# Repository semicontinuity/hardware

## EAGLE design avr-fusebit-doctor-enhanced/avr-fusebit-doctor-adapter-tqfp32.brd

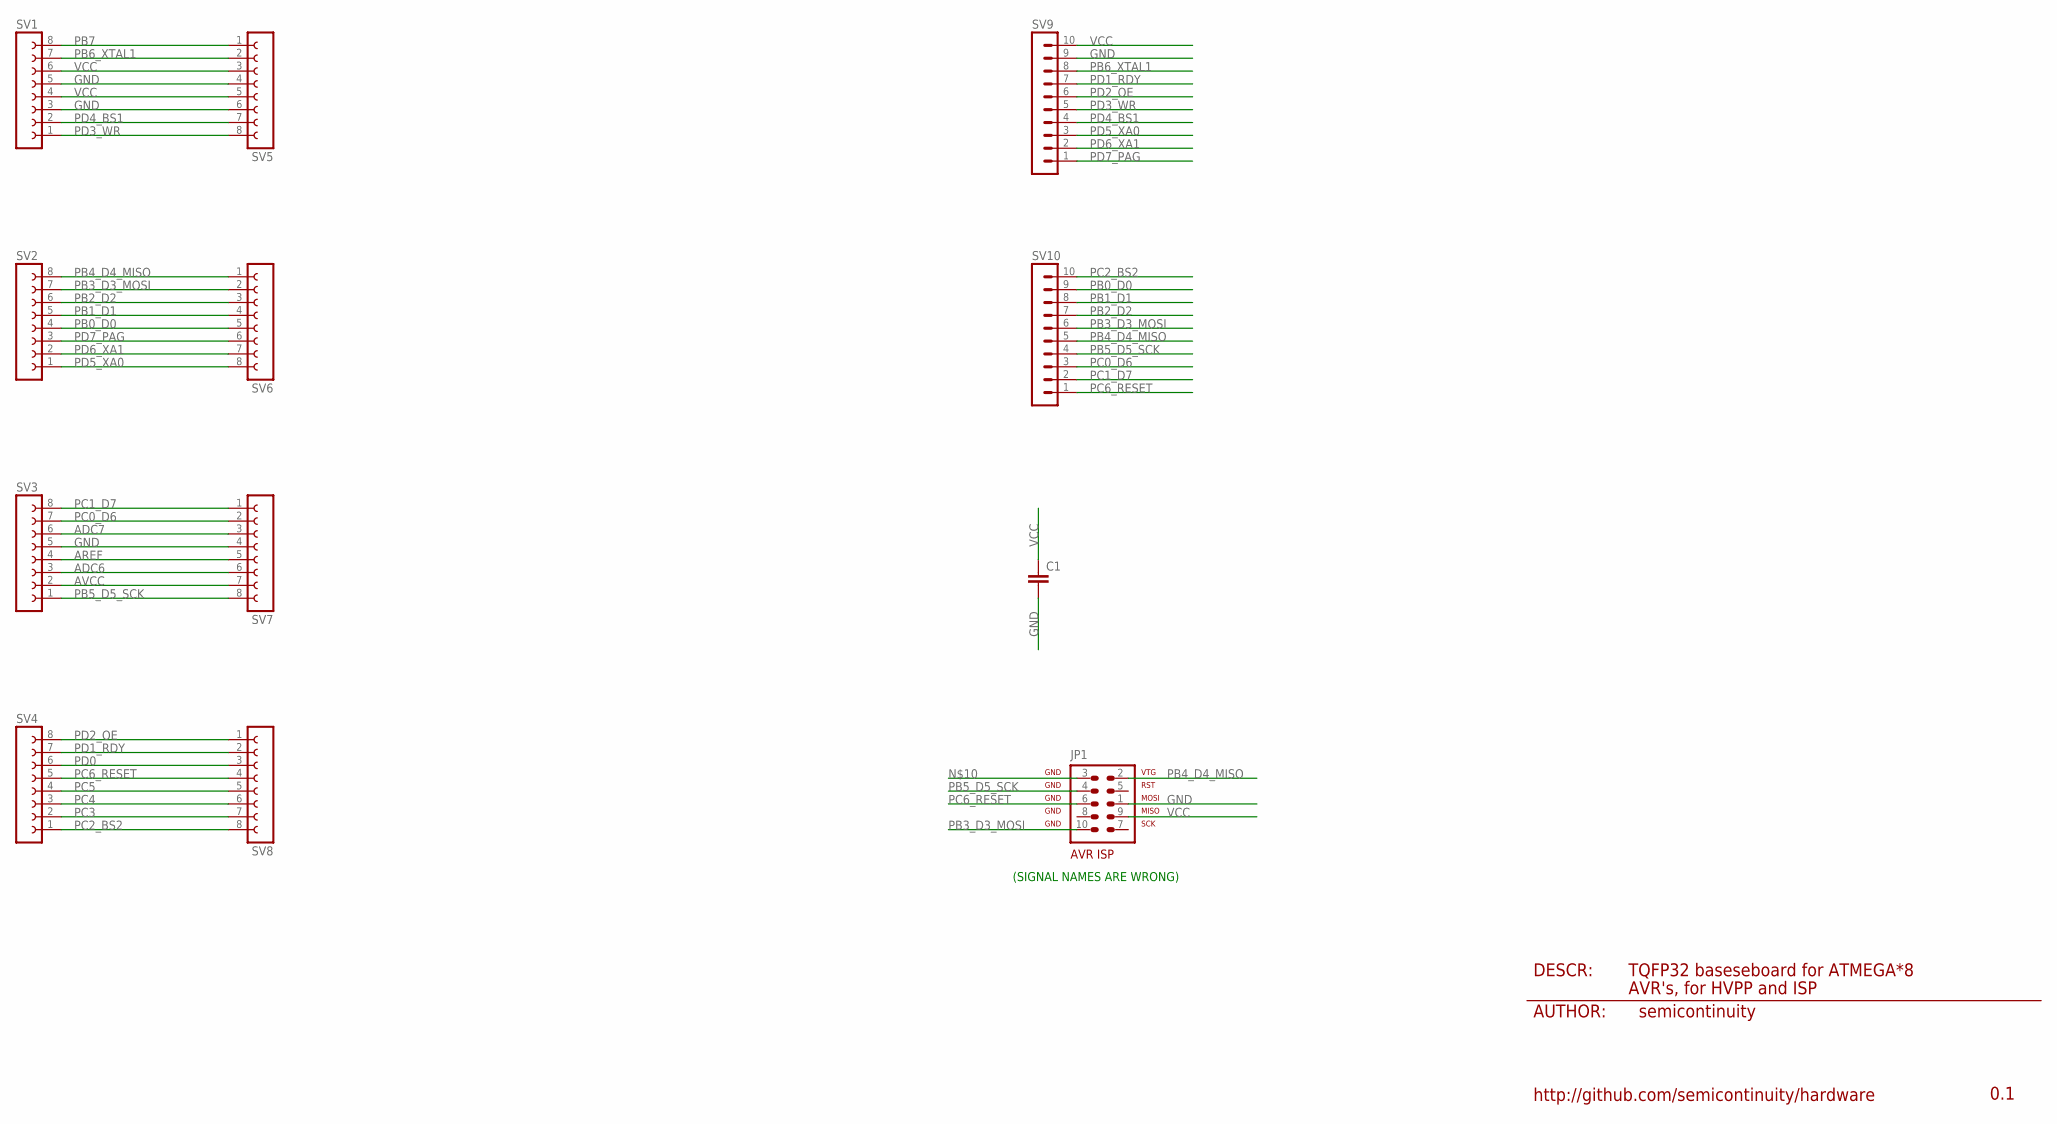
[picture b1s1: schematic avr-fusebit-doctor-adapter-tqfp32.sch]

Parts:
C1: C-EUC0805; C0805
JP1: AVR-ISP-10
SV1, SV2, SV3, SV4, SV5, SV6, SV7, SV8: FE08-1; FE08
SV9, SV10: MA10-1

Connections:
ADC6: SV3.3, SV7.6
ADC7: SV3.6, SV7.3
AREF: SV3.4, SV7.5
AVCC: SV3.2, SV7.7
GND: C1.2, JP1.1, SV1.3, SV1.5, SV3.5, SV5.4, SV5.6, SV7.4, SV9.9
PB0_D0: SV2.4, SV6.5, SV10.9
PB1_D1: SV2.5, SV6.4, SV10.8
PB2_D2: SV2.6, SV6.3, SV10.7
PB3_D3_MOSI: JP1.10, SV2.7, SV6.2, SV10.6
PB4_D4_MISO: JP1.2, SV2.8, SV6.1, SV10.5
PB5_D5_SCK: JP1.4, SV3.1, SV7.8, SV10.4
PB6_XTAL1: SV1.7, SV5.2, SV9.8
PB7: SV1.8, SV5.1
PC0_D6: SV3.7, SV7.2, SV10.3
PC1_D7: SV3.8, SV7.1, SV10.2
PC2_BS2: SV4.1, SV8.8, SV10.10
PC3: SV4.2, SV8.7
PC4: SV4.3, SV8.6
PC5: SV4.4, SV8.5
PC6_RESET: JP1.6, SV4.5, SV8.4, SV10.1
PD0: SV4.6, SV8.3
PD1_RDY: SV4.7, SV8.2, SV9.7
PD2_OE: SV4.8, SV8.1, SV9.6
PD3_WR: SV1.1, SV5.8, SV9.5
PD4_BS1: SV1.2, SV5.7, SV9.4
PD5_XA0: SV2.1, SV6.8, SV9.3
PD6_XA1: SV2.2, SV6.7, SV9.2
PD7_PAG: SV2.3, SV6.6, SV9.1
VCC: C1.1, JP1.9, SV1.4, SV1.6, SV5.3, SV5.5, SV9.10

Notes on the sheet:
AUTHOR:
DESCR:
TQFP32 baseseboard for ATMEGA*8
AVR's, for HVPP and ISP
semicontinuity
0.1
http://github.com/semicontinuity/hardware
(SIGNAL NAMES ARE WRONG)

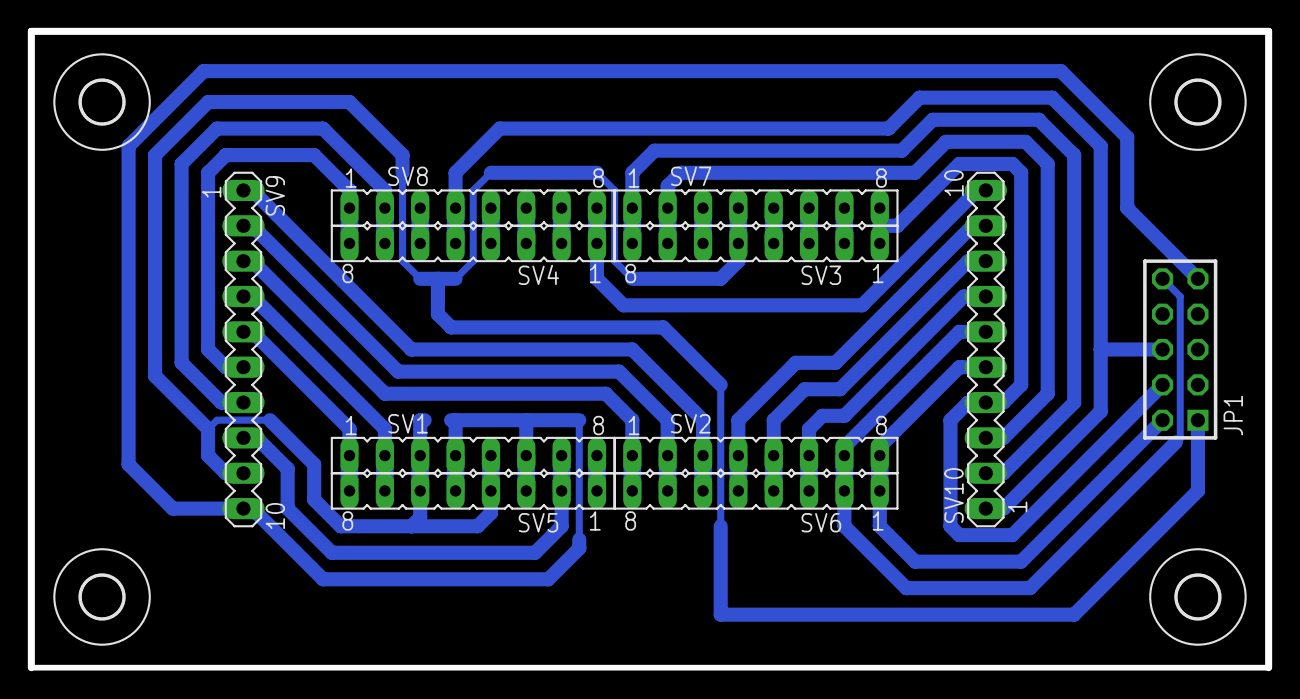
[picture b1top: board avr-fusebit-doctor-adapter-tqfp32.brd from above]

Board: 2 copper layers, 88.9 x 45.7 mm, 16 parts (1 on the bottom side), 29 nets.

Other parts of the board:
U$1, U$2, U$3, U$4: 3,0

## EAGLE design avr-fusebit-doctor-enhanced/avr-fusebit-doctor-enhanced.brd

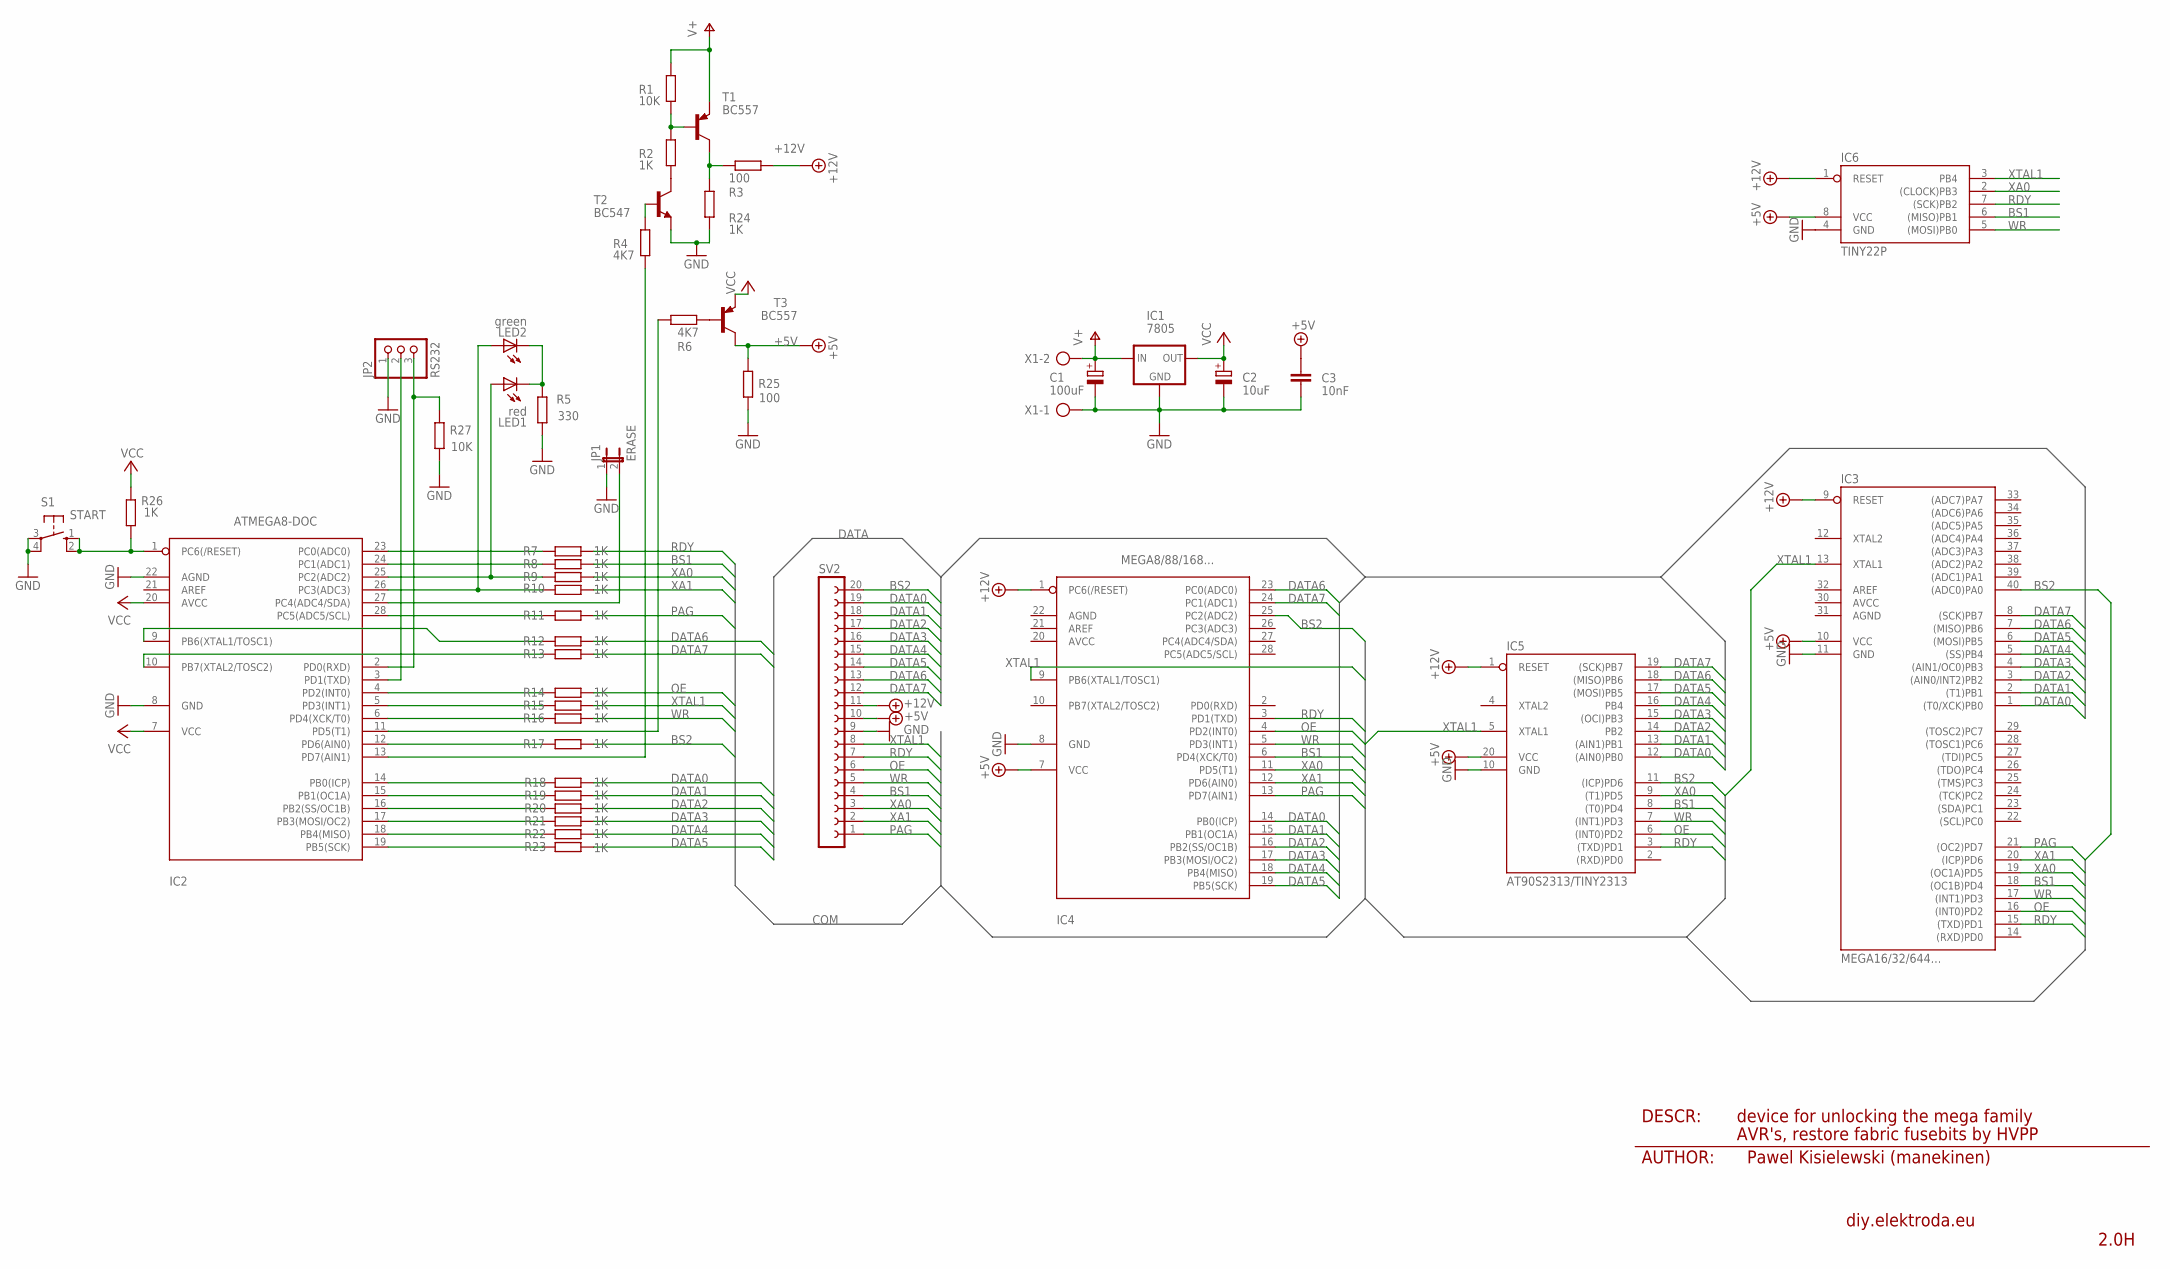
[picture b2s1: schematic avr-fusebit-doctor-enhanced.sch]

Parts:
C1: 100uF; E2,5-5
C2: 10uF; E2,5-5
C3: 10nF; C050-024X044
IC1: 7805; 78XXL
IC2: ATMEGA8-DOC; DIL28-3
IC3: MEGA16/32/644...; DIL40
IC4: MEGA8/88/168...; DIL28-3
IC5: AT90S2313/TINY2313; DIL20
IC6: TINY22P; DIL08
JP1: ERASE; JP1
JP2: RS232; 1X03
LED1: red; LED3MM
LED2: green; LED3MM
R1, R27: 10K; 0204/5
R2, R7, R8, R9, R10, R11, R12, R13, R14, R15, R16, R17, R18, R19, R20, R21, R22, R23, R24, R26: 1K; 0204/5
R3, R25: 100; 0204/5
R4, R6: 4K7; 0204/5
R5: 330; 0204/5
S1: START; B3F-10XX
SV2: FE20-1; FE20
T1, T3: BC557; TO92-EBC
T2: BC547; TO92-EBC
X1: AK500/2

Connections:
+5V: C3.1, IC3.10 (VCC), IC4.7 (VCC), IC5.20 (VCC), IC6.8 (VCC), R25.2, SV2.10, T3.C
+12V: IC3.9 (RESET), IC4.1 (PC6(/RESET)), IC5.1 (RESET), IC6.1 (RESET), R3.2, SV2.11
AGND: IC3.31 (AGND)
AREF: IC3.32 (AREF)
AVCC: IC3.30 (AVCC)
BS1: IC3.18 ((OC1B)PD4), IC4.6 (PD4(XCK/T0)), IC5.8 ((T0)PD4), IC6.6 ((MISO)PB1), R8.2, SV2.4
BS2: IC3.40 ((ADC0)PA0), IC4.25 (PC2(ADC2)), IC5.11 ((ICP)PD6), R17.2, SV2.20
DATA0: IC3.1 ((T0/XCK)PB0), IC4.14 (PB0(ICP)), IC5.12 ((AIN0)PB0), R18.2, SV2.19
DATA1: IC3.2 ((T1)PB1), IC4.15 (PB1(OC1A)), IC5.13 ((AIN1)PB1), R19.2, SV2.18
DATA2: IC3.3 ((AIN0/INT2)PB2), IC4.16 (PB2(SS/OC1B)), IC5.14 (PB2), R20.2, SV2.17
DATA3: IC3.4 ((AIN1/OC0)PB3), IC4.17 (PB3(MOSI/OC2)), IC5.15 ((OCI)PB3), R21.2, SV2.16
DATA4: IC3.5 ((SS)PB4), IC4.18 (PB4(MISO)), IC5.16 (PB4), R22.2, SV2.15
DATA5: IC3.6 ((MOSI)PB5), IC4.19 (PB5(SCK)), IC5.17 ((MOSI)PB5), R23.2, SV2.14
DATA6: IC3.7 ((MISO)PB6), IC4.23 (PC0(ADC0)), IC5.18 ((MISO)PB6), R12.2, SV2.13
DATA7: IC3.8 ((SCK)PB7), IC4.24 (PC1(ADC1)), IC5.19 ((SCK)PB7), R13.2, SV2.12
GND: C1.-, C2.-, C3.2, IC1.GND, IC2.8 (GND), IC2.22 (AGND), IC3.11 (GND), IC4.8 (GND), IC5.10 (GND), IC6.4 (GND), JP1.1, JP2.1, R5.1, R24.1, R25.1, R27.2, S1.3, S1.4 (P1), SV2.9, T2.E, X1.1
unnamed: R6.1, T3.B
unnamed: IC2.14 (PB0(ICP)), R18.1
unnamed: IC2.3 (PD1(TXD)), JP2.2
unnamed: IC2.28 (PC5(ADC5/SCL)), R11.1
unnamed: IC2.6 (PD4(XCK/T0)), R16.1
unnamed: IC2.4 (PD2(INT0)), R14.1
unnamed: IC2.2 (PD0(RXD)), JP2.3, R27.1
unnamed: R2.2, T2.C
unnamed: IC2.9 (PB6(XTAL1/TOSC1)), R12.1
unnamed: IC2.10 (PB7(XTAL2/TOSC2)), R13.1
unnamed: IC2.13 (PD7(AIN1)), R4.2
unnamed: IC2.11 (PD5(T1)), R6.2
unnamed: IC2.15 (PB1(OC1A)), R19.1
unnamed: IC2.16 (PB2(SS/OC1B)), R20.1
unnamed: IC2.5 (PD3(INT1)), R15.1
unnamed: IC2.23 (PC0(ADC0)), R7.1
unnamed: R3.1, R24.2, T1.C
unnamed: IC2.17 (PB3(MOSI/OC2)), R21.1
unnamed: IC2.18 (PB4(MISO)), R22.1
unnamed: IC2.19 (PB5(SCK)), R23.1
unnamed: IC2.12 (PD6(AIN0)), R17.1
unnamed: R4.1, T2.B
unnamed: IC2.27 (PC4(ADC4/SDA)), JP1.2
unnamed: LED1.K (C), LED2.K (C), R5.2
unnamed: R1.2, R2.1, T1.B
unnamed: IC2.24 (PC1(ADC1)), R8.1
unnamed: IC2.1 (PC6(/RESET)), R26.1, S1.1 (S), S1.2 (S1)
unnamed: IC2.26 (PC3(ADC3)), LED2.A, R10.1
unnamed: IC2.25 (PC2(ADC2)), LED1.A, R9.1
OE: IC3.16 ((INT0)PD2), IC4.4 (PD2(INT0)), IC5.6 ((INT0)PD2), R14.2, SV2.6
PAG: IC3.21 ((OC2)PD7), IC4.13 (PD7(AIN1)), R11.2, SV2.1
RDY: IC3.15 ((TXD)PD1), IC4.3 (PD1(TXD)), IC5.3 ((TXD)PD1), IC6.7 ((SCK)PB2), R7.2, SV2.7
V+: C1.+, IC1.IN, R1.1, T1.E, X1.2
VCC: C2.+, IC1.OUT, IC2.7 (VCC), IC2.20 (AVCC), R26.2, T3.E
WR: IC3.17 ((INT1)PD3), IC4.5 (PD3(INT1)), IC5.7 ((INT1)PD3), IC6.5 ((MOSI)PB0), R16.2, SV2.5
XA0: IC3.19 ((OC1A)PD5), IC4.11 (PD5(T1)), IC5.9 ((T1)PD5), IC6.2 ((CLOCK)PB3), R9.2, SV2.3
XA1: IC3.20 ((ICP)PD6), IC4.12 (PD6(AIN0)), R10.2, SV2.2
XTAL1: IC3.13 (XTAL1), IC4.9 (PB6(XTAL1/TOSC1)), IC5.5 (XTAL1), IC6.3 (PB4), R15.2, SV2.8

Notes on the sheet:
AUTHOR:
DESCR:
device for unlocking the mega family
AVR's, restore fabric fusebits by HVPP
Pawel Kisielewski (manekinen)
2.0H
diy.elektroda.eu

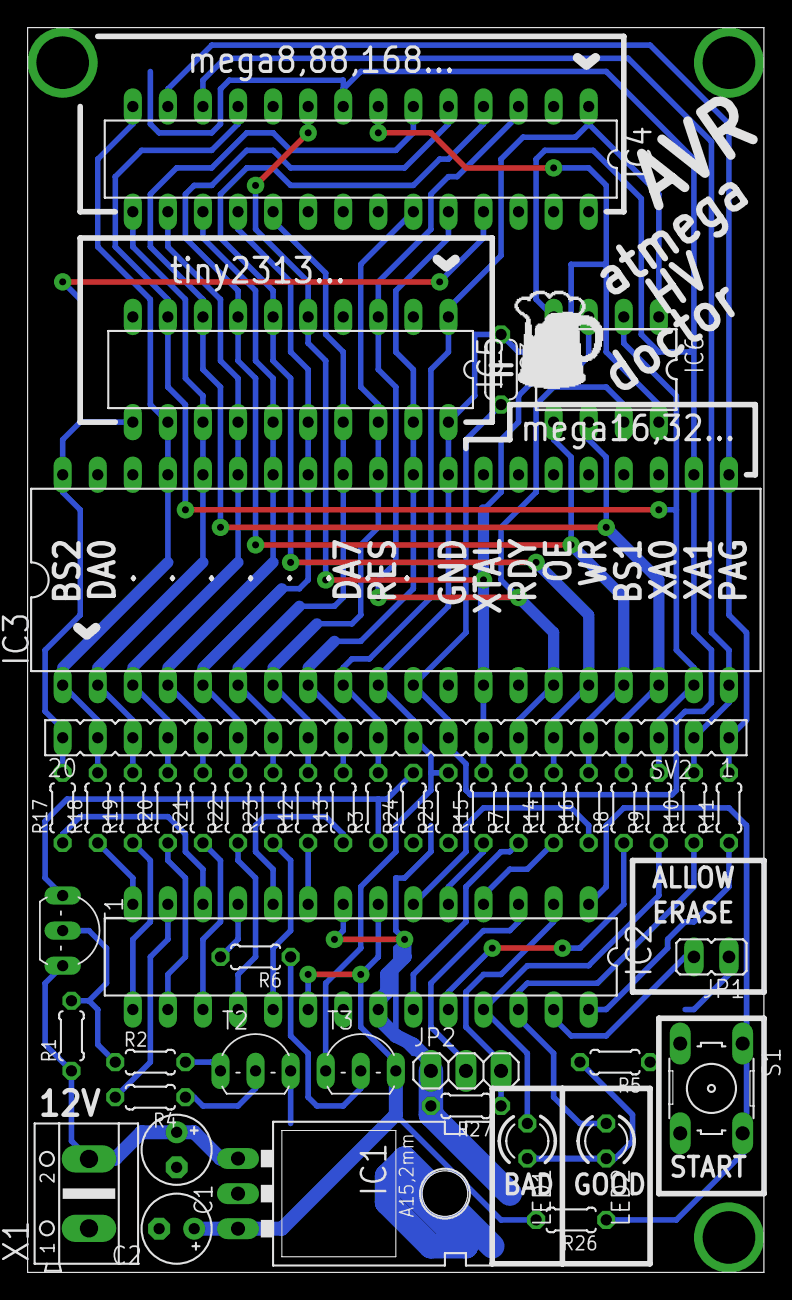
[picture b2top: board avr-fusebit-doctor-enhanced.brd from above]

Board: 2 copper layers, 53.3 x 90.2 mm, 46 parts (0 on the bottom side), 51 nets.

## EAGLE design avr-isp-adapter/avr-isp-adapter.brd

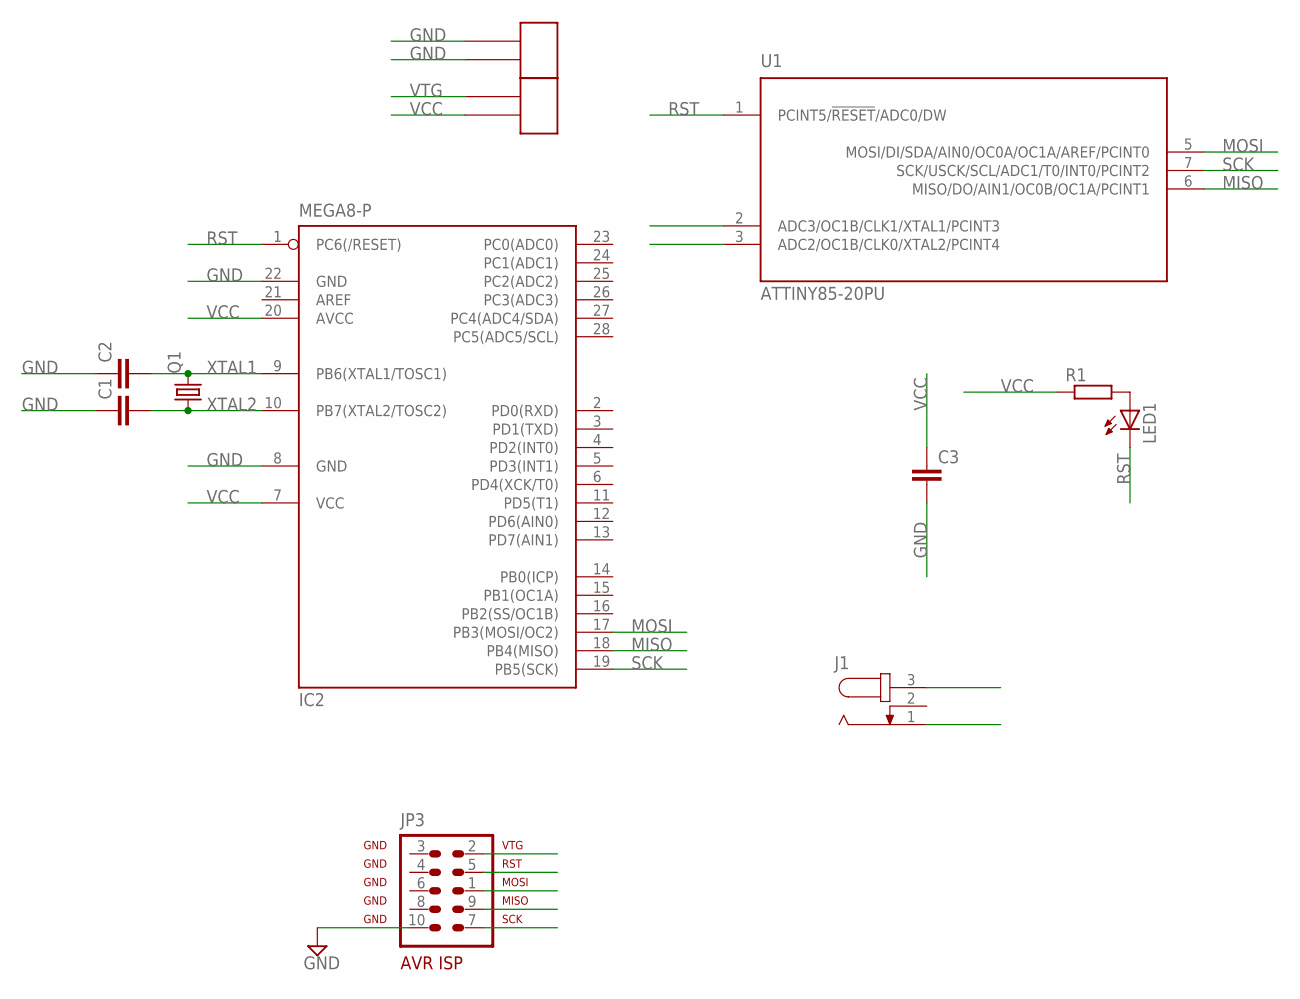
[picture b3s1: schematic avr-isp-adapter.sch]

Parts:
C1, C2, C3: C-EUC0805; C0805
IC2: MEGA8-P; DIL28-3
J1: JACK-PLUG1; SPC4078
JP3: AVR-ISP-10
LED1: LED3MM
Q1: CRYSTALHC49S; HC49/S
R1: R-EU_M0805; M0805
U1: ATTINY85-20PU; DIP-8
U$1, U$2: MA02-1

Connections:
GND: C1.1, C2.1, C3.2, IC2.8 (GND), IC2.22 (GND), J1.1, JP3.10, U1.4 (GND), U$2.P1, U$2.P2
MISO: IC2.18 (PB4(MISO)), JP3.9, U1.6 (MISO/DO/AIN1/OC0B/OC1A/PCINT1)
MOSI: IC2.17 (PB3(MOSI/OC2)), JP3.1, U1.5 (MOSI/DI/SDA/AIN0/OC0A/OC1A/AREF/PCINT0)
unnamed: LED1.A, R1.2
RST: IC2.1 (PC6(/RESET)), JP3.5, LED1.K (C), U1.1 (PCINT5/!RESET!/ADC0/DW)
SCK: IC2.19 (PB5(SCK)), JP3.7, U1.7 (SCK/USCK/SCL/ADC1/T0/INT0/PCINT2)
VCC: C3.1, IC2.7 (VCC), IC2.20 (AVCC), J1.3, R1.1, U1.8 (VCC), U$1.P2
VTG: JP3.2, U$1.P1
XTAL1: C2.2, IC2.9 (PB6(XTAL1/TOSC1)), Q1.2, U1.2 (ADC3/OC1B/CLK1/XTAL1/PCINT3)
XTAL2: C1.2, IC2.10 (PB7(XTAL2/TOSC2)), Q1.1, U1.3 (ADC2/OC1B/CLK0/XTAL2/PCINT4)

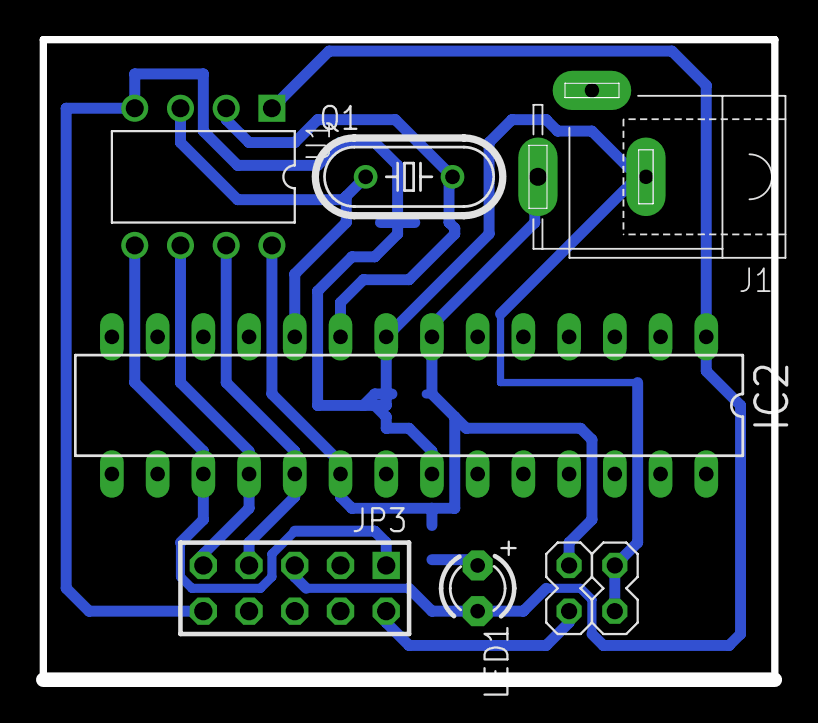
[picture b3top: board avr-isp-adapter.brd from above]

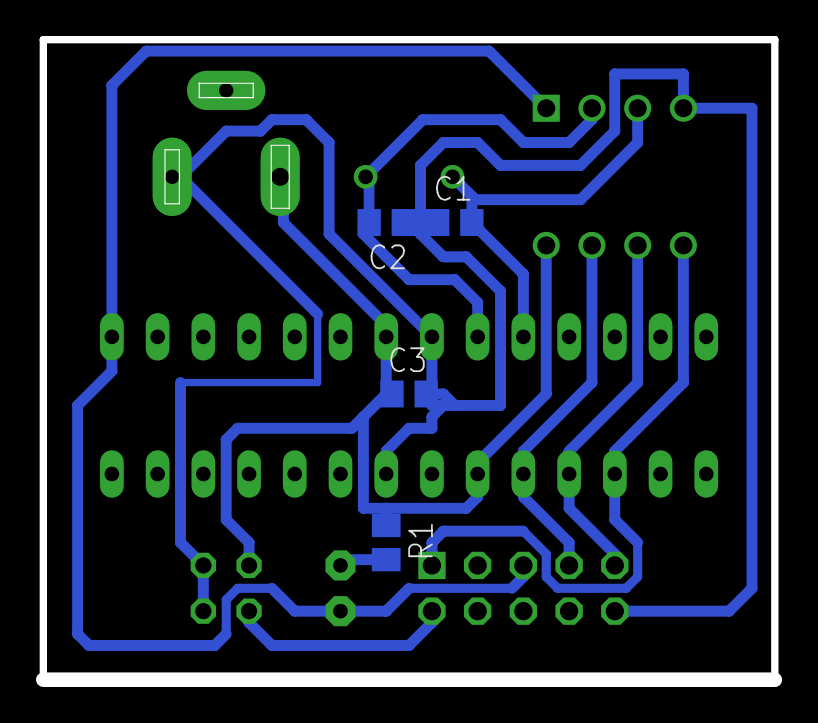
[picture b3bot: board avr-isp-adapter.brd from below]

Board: 2 copper layers, 40.6 x 35.6 mm, 12 parts (4 on the bottom side), 10 nets.

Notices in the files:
parts and their libraries:
volks73-Atmel: Creative Commons Attribution-ShareAlike 3.0 Unported (CC BY-SA 3.0), http://creativecommons.org/licenses/by-sa/3.0/.
